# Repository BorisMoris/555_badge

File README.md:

# 555_badge

Custom PCB created in KiCad while following [An Intro to KiCad tutorial](https://www.youtube.com/watch?v=vaCVh2SAZY4&list=PL3bNyZYHcRSUhUXUt51W6nKvxx2ORvUQB)
by DigiKey and Shawn Hymel.

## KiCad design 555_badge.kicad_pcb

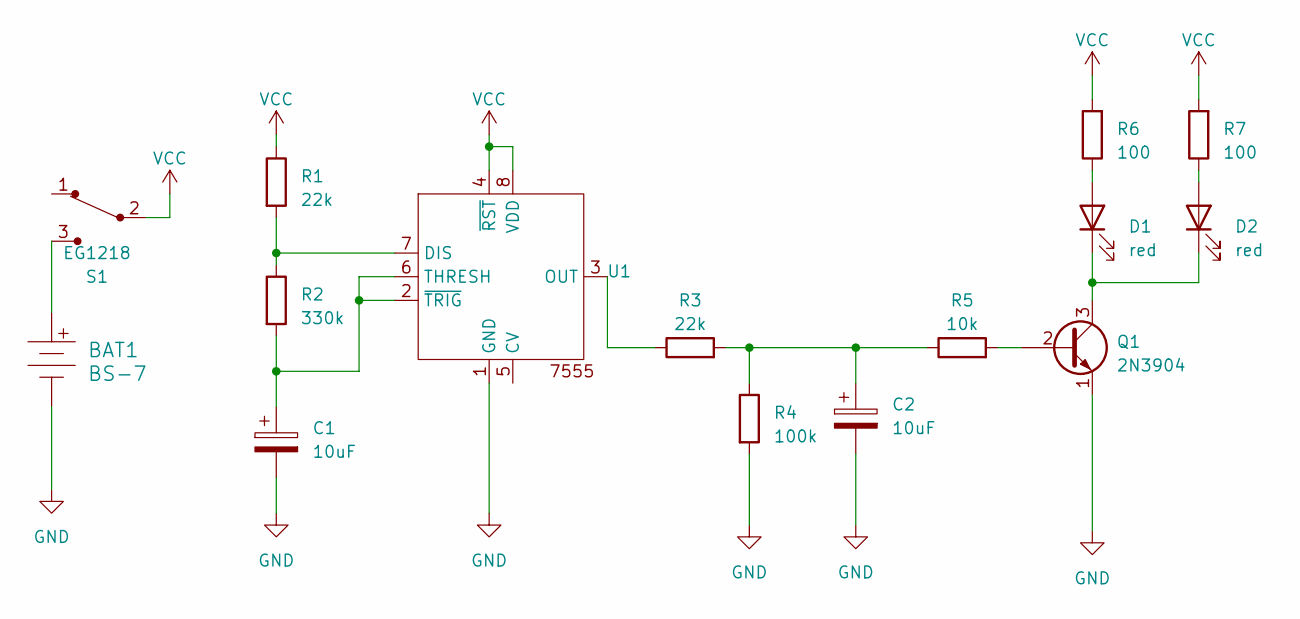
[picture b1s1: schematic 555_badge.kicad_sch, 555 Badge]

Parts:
BAT1: BS-7; Battery_Holder_Coin_2032_BS-7; MPN BS-7; Digi-Key_PN BS-7-ND
C1: 10uF; CP_Radial_D5.0mm_P2.00mm
C2: 10uF; CP_Radial_D6.3mm_P2.50mm
D1, D2: red; LED_D3.0mm
Q1: 2N3904; TO-92-3
R1, R3: 22k; R_Axial_DIN0207_L6.3mm_D2.5mm_P10.16mm_Horizontal
R2: 330k; R_Axial_DIN0207_L6.3mm_D2.5mm_P10.16mm_Horizontal
R4: 100k; R_Axial_DIN0207_L6.3mm_D2.5mm_P10.16mm_Horizontal
R5: 10k; R_Axial_DIN0207_L6.3mm_D2.5mm_P10.16mm_Horizontal
R6, R7: 100; R_Axial_DIN0207_L6.3mm_D2.5mm_P10.16mm_Horizontal
S1: EG1218; Switch_Slide_11.6x4mm_EG1218; MPN EG1218; Digi-Key_PN EG1903-ND
U1: ICM7555-PDIP

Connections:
GND: BAT1.Neg, C1.2, C2.2, Q1.1 (E), R4.2, U1.1 (GND)
unnamed: BAT1.Pos, S1.3
unnamed: C2.1, R3.2, R4.1, R5.1
unnamed: D1.2 (A), R6.1
unnamed: D1.1 (K), D2.1 (K), Q1.3 (C)
unnamed: D2.2 (A), R7.1
unnamed: Q1.2 (B), R5.2
unnamed: R1.2, R2.1, U1.7 (DIS)
unnamed: R3.1, U1.3 (OUT)
unnamed: C1.1, R2.2, U1.2 (~TRIG), U1.6 (THRESH)
VCC: R1.1, R6.2, R7.2, S1.2, U1.4 (~RST), U1.8 (VDD)

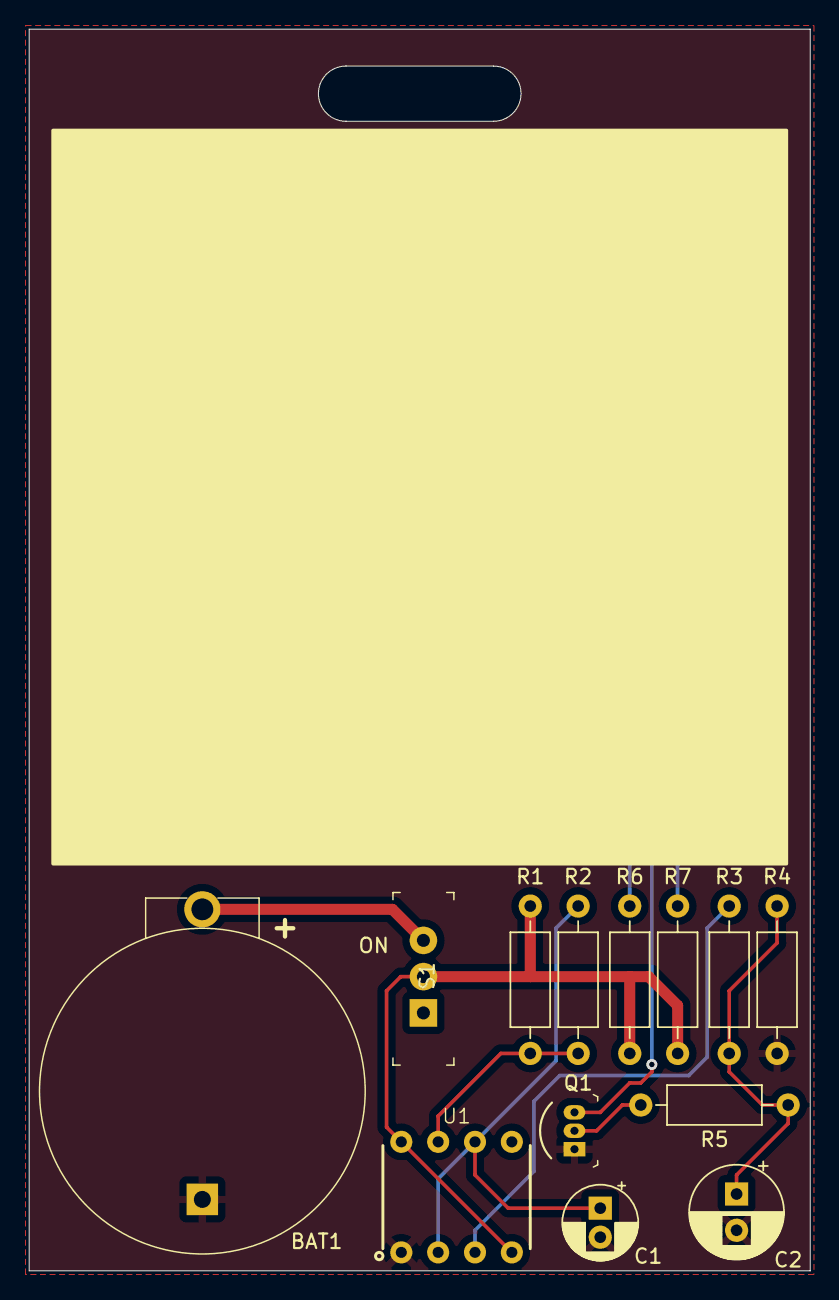
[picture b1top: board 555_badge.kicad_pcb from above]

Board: 2 copper layers, 53.8 x 85.6 mm, 15 parts (0 on the bottom side), 11 nets.

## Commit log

2023-03-10 Inital commit

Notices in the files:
555_badge.kicad_sch:
creativecommons.org/licenses/by/4.0
licencse: CC BY 4.0
